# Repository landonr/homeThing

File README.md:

<h1 align = "center">homeThing Remote ⚙️</h1>
<h5 align = "center">(esphome remote)</h5>
<p align="center">

</p>

<br>
<div align="center">
	<h2>This project is no longer in active development</h2>
	<p>The homeThing S3 can still be <a href="https://www.pcbway.com/project/shareproject/homeThing_S3_2b3ac3ac.html">ordered fully assembled from PCBWay</a>. The code, case files, and PCB files stay here for anyone who wants to build their own.</p>
	<h3>The successor is <a href="https://github.com/landonr/homething-c6">homeThing C6</a></h3><p>a universal remote with a scroll wheel. It has no screen, better battery life, and also sponsored by PCBWay.</p>
</div>
<hr>

#### homeThing is a collection of software and hardware for creating universal remotes that control smart home devices.
There are 3 components that belong to homeThing: the case and circuit board, the menu system code, and the code to control smart home devices
- <a href="#hardware-">Hardware specific for smart home remotes that's open source, customizable, and 3D printable.</a>
- <a href="#homething-menu-">Menu system for ESP32 devices focused on controlling smart home devices similar to an iPod's menu.</a>
- [ESPHome Components for controlling Home Assistant devices.](https://github.com/landonr/esphome-components)

### Learn More
 - [Get Started](GettingStarted.md) - Learn how to build your own remote
 - [Discord](https://discord.gg/BX6ZtGKHTy) - support / chat with the community and the team
 - [Instagram](https://www.instagram.com/homething.io/) - Follow along on Instagram
 - [Website](https://homething.io) - Check out our website for more information

<div align="center">
	<h3>
	<a href="https://youtu.be/5bx5w-n5c0Y">
		
		<br>Demo Video - Watch on YouTube 🎬
	</a>
	</h3>
</div>

# Hardware 💪
We designed the two remotes below to be ideal for controlling smart home devices without a touch screen. They are both battery-powered but can also be plugged into USB and left in one place. The first remote was based on a Lilygo TDisplay. We moved on to the homeThing S3 because the original device had slow performance, lacked buttons, and had challenges with assembly. Neither is in active development anymore; work has moved to [homeThing C6](https://github.com/landonr/homething-c6).
<table>
  <tr>
    <th>
	    <h3>TDisplay homeThing</h3>
    </th>
    <th>
	    <h3>TDisplay S3 homeThing</h3>
	    <a href="https://github.com/landonr/homeThing/tree/main/Case%20Design/tdisplay-s3">More Info</a><br>
    </th>
  </tr>
  <tr>
    <td></td>
    <td></td>

  </tr>
  <tr>
	  <td>Not available for purchase</td>
	  <td>No longer developed, still available fully assembled from PCBWay</td>
  </tr>
  <tr>
    <td><a href="https://www.pcbway.com/project/shareproject/homeThing_V1_3_e3572f8f.html">Order Case from PCBWay</a></td>
    <td>
      <a href="https://www.pcbway.com/project/shareproject/homeThing_S3_2b3ac3ac.html">Order parts or fully assembled from PCBWay</a>
    </td>
  </tr>
  <tr>
    <td></td>
    <td>Sold: 27 assembled, 32 PCBs, 10 cases</td>
  </tr>
  <tr>
    <td><a href="https://github.com/landonr/homeThing/tree/main/Case%20Design">Case 3D Files</a></td>
    <td><a href="https://github.com/landonr/homeThing/tree/main/Case%20Design">Case 3D Files</a></td>
  </tr>
  <tr>
    <td><a href="tdisplay-ipod.yaml">ESPHome Config</a></td>
    <td><a href="tdisplay-s3.yaml">ESPHome Config</a></td>
  </tr>
  <tr>
  	<td>
	<h4>Features</h4>
	<ul>
		<li>Based on Lilygo TTGo TDisplay, an ESP32 with integrated screen
		<li>Low cost remote with minimal parts</li>
		<li>Scroll wheel and 2 configurable buttons</li>
		<li>USB-C Charging</li>
		<li>3D Printable case with 3 parts</li>
	</ul>
	</td>
  	<td>
	<h4>Features</h4>
	<ul>
		<li>Based on Lilygo TDisplay S3, an ESP32 S3 with integrated screen</li>
		<li>Faster processor and larger display</li>
		<li>Custom PCB for easier setup</li>
		<li>IR Blaster for controlling infrared devices</li>
		<li>Internal microphone for Voice Assistant</li>
		<li>Scroll wheel and 5 configurable buttons</li>
		<li>USB-C Charging</li>
		<li>3D Printable case with 2 parts</li>
	</ul>
	</td>
  </tr>
</table>

We made a couple of custom devices for running homeThing, but it can also run on almost any ESP32 such as,
- M5Stack Fire
- M5Stick C
- Lilygo T4
- Lilygo T-Display TTGO
- Lilygo T-Display S3
- Lilygo T-Display S3 AMOLED
# homeThing Menu 📝
### ESPHome menu system that requires minimal config. Features apps which have custom UIs
|t-display demo|m5stack fire demo|lilygo T4 demo|
|--|--|--|
|||

- Scroll through list and press center to select
- With a scrollwheel the top button goes back
- On M5Stack going up past the top of the list will go back
- A scroll bar appears if list extends past the screen. 
- Screen returns to now playing after display sleeps
    - Display sleeps after 10s of idle. Device sleeps after 2h of idle 💤
- Font size and UI size is adjustable in yaml 🔨
- Simple yaml configuration. all of the complicated code is included in other files 🛠
- Header is always shown at the top with info about the current state

## Apps
### Now playing screen ⏯

<ul>
<li>Control media players using the scroll wheel buttons</li>
<li>Scroll for volume using the scroll wheel</li>
</ul>

|Music|TV|
|--|--|
|<ul><li>Control smart speakers like Sonos, Spotify, or Google Home</li><li>Change source from Spotify playlists, Sonos Favorites, and custom lists</li><li>Manage speaker groups</li></ul>|<ul><li>Menu navigation such as up, down, left, right, select (with scroll wheel)</li><li>Power, back, home, pause in second menu</li><li>Change source from tv source list</li><li>Optional soundbar support</li></ul>|

### IR Remote
<ul>
<li>Custom UI and buttons to control infrared cat toys</li>
</ul>

### Games
<ul>
<li>Snake</li>
<li>Breakout</li>
</ul>

# Mentions
- Home Assistant Voice Contest - Best Starting Guide https://www.home-assistant.io/blog/2024/03/16/voice-assistant-community-contest-winners-annoucement/
- Hackaday https://hackaday.com/2022/09/08/scroll-through-esphome-with-ipod-style-click-wheel/
- Hackster https://www.hackster.io/news/ipod-style-esphome-remote-3ca38edab2b4
- Reddit post https://www.reddit.com/r/homeassistant/comments/x59dcp/i_built_an_ipod_style_esphome_remote_for_home/
- Self Hosted - Episode 80 - Solving Whole Home Audio (around 30:00) https://selfhosted.show/80 

# Includes
- <a href="https://esphome.io/">ESPHome</a>
- <a href="https://github.com/be5invis/Iosevka">Iosevka Font</a>
- [@ssieb](https://github.com/ssieb)'s <a href="https://github.com/ssieb/custom_components/tree/master/components/ip5306">IP5306 esphome component</a>
- <a href="https://github.com/landonr/esphome-components">homeThing ESPHome Components</a>

# Sponsorship

## [PCBWay](https://pcbway.com/g/Xymq6O "PCBWay") sponsored 3D Printing and PCB assembly costs on this project during the prototyping phase, and also sponsors [homeThing C6](https://github.com/landonr/homething-c6)!
If you are interested in their awesome fabrication services please check them out. They offer 3D prototyping, PCB design and assembly, as well as CNC metal fabrication. Costs are reasonable and the quality is as good as it gets. Thank you PCBWay for sponsoring us and other fun projects!<br><br>

## [cargo](https://cargo.site/ "cargo.site") sponsors our website!

They make it super easy to keep things pretty and up to date! It’s honestly so much easier than managing our own site, highly recommended!

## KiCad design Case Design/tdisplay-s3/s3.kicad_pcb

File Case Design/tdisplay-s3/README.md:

<h2>TDisplay S3 homeThing</h2>

This remote is no longer in active development. It can still be <a href="https://www.pcbway.com/project/shareproject/homeThing_S3_2b3ac3ac.html">ordered fully assembled from PCBWay</a>, and the files stay here for DIY builds. The successor is <a href="https://github.com/landonr/homething-c6">homeThing C6</a>, a universal remote with a scroll wheel, no screen, and better battery life.

<table>
    <tr>
        <th>TDisplay S3<br>homeThing Case</th>
        <th>homeThing S3<br>Circuit Front</th>
        <th>homeThing S3<br>Circuit Back</th>
    </tr>
    <tr>
        <td>
            
        </td>
        <td>
            
        </td>
        <td>
            
        </td>
    </tr>
</table>

<h2>Order</h2>
<a href="https://www.pcbway.com/project/shareproject/homeThing_S3_2b3ac3ac.html">Order Case and PCB from PCBWay</a>

Sold: 27 assembled, 32 PCBs, 10 cases

<h2>Case 3D Files</h2>
There's a separate front file for FDM printers. It has no extruded buttons, so it prints flat without supports.
<table>
    <tr>
        <th>Front (SLS)</th>
        <th>Front (FDM)</th>
        <th>Back</th>
    </tr>
    <tr>
        <td><a href="s3%20case%20front%20sls.stl">s3 case front sls.stl</a></td>
        <td><a href="s3%20case%20front%20fdm.stl">s3 case front fdm.stl</a></td>
        <td><a href="s3%20case%20back.stl">s3 case back.stl</a></td>
    </tr>
</table>

<h2>Circuit</h2>
<a href="gerber/">Gerber Files</a>

<h2>ESPHome Config</h2>
<a href="../../tdisplay-s3.yaml">tdisplay-s3.yaml</a>

<h2>Parts</h2>
<table>
    <tr>
        <th>Name</th>
        <th>Qty</th>
        <th>Description</th>
    </tr>
    <tr>
        <td><a href="https://www.pcbway.com/project/shareproject/homeThing_S3_2b3ac3ac.html">Custom PCB</a></td>
        <td>1</td>
        <td>Custom homeThing S3 PCB. Gerbers are in <a href="gerber/">gerber/</a>.</td>
    </tr>
    <tr>
        <td><a href="https://www.lilygo.cc/en-ca/products/t-display-s3?variant=42351558590645">TDisplay S3 (Soldered Pin)</a></td>
        <td>1</td>
        <td>ESP32-S3 board with screen. Plugs into the PCB.</td>
    </tr>
    <tr>
        <td><a href="https://www.adafruit.com/product/5001">Adafruit ANO Directional Navigation and Scroll Wheel Rotary Encoder</a></td>
        <td>1</td>
        <td>Directional buttons and scroll wheel</td>
    </tr>
    <tr>
        <td><a href="https://www.adafruit.com/product/5221">Adafruit ANO Rotary Navigation Encoder Breakout PCB</a></td>
        <td>1</td>
        <td>Breakout for the ANO encoder. Plugs into the PCB.</td>
    </tr>
    <tr>
        <td><a href="https://www.aliexpress.us/item/32962426410.html">INMP441</a></td>
        <td>1</td>
        <td>I2S microphone</td>
    </tr>
    <tr>
        <td><a href="https://leeselectronic.com/en/product/71446-ic-i-o-expander-for-i2c-8bit-pcf8574p.html">PCF8574N</a></td>
        <td>1</td>
        <td>I2C GPIO expander for the ANO and case buttons</td>
    </tr>
    <tr>
        <td><a href="https://www.adafruit.com/product/387">5mm 940nm IR LED</a></td>
        <td>1</td>
        <td>IR transmitter on GPIO13</td>
    </tr>
    <tr>
        <td><a href="https://leeselectronic.com/qc/product/7174-7174TRANSISTOR2N2222MPS2222ANPN5.html">2N2222 NPN transistor</a></td>
        <td>1</td>
        <td>IR LED driver</td>
    </tr>
    <tr>
        <td><a href="https://leeselectronic.com/en/product/91581-91581RESISTORS14W470OHM110PCS.html">470ohm resistor</a></td>
        <td>1</td>
        <td>IR LED current limit</td>
    </tr>
    <tr>
        <td><a href="https://leeselectronic.com/en/product/844-polyester-cap-50v-01uf-4pcs.html">0.1uF capacitor</a></td>
        <td>1</td>
        <td>Decoupling for the PCF8574</td>
    </tr>
    <tr>
        <td><a href="https://leeselectronic.com/en/product/31231-tack-switch-6x6x10mm.html">6x6mm tactile switch (10mm tall)</a></td>
        <td>3</td>
        <td>Through-hole tact switches for the case buttons</td>
    </tr>
    <tr>
        <td><a href="https://www.aliexpress.com/item/32835179410.html">3.7V 7x20x50mm 700mAh Lipo</a></td>
        <td>1</td>
        <td>Battery</td>
    </tr>
    <tr>
        <td><a href="https://leeselectronic.com/en/product/6049-6049BOLTM25100PCS.html">M2.5x8mm screws</a></td>
        <td>6</td>
        <td>Case screws</td>
    </tr>
    <tr>
        <td>Female pin socket 1x12, 2.54mm</td>
        <td>2</td>
        <td>T-Display S3 plugs into these</td>
    </tr>
    <tr>
        <td>Female pin socket 1x09, 2.54mm</td>
        <td>1</td>
        <td>ANO breakout plugs into this</td>
    </tr>
    <tr>
        <td>Female pin socket 1x03, 2.54mm</td>
        <td>2</td>
        <td>INMP441 plugs into these</td>
    </tr>
    <tr>
        <td>Male pin header 1x04, 2.54mm (optional)</td>
        <td>1</td>
        <td>Optional expansion header: 5V, GPIO12, GPIO16, GND</td>
    </tr>
</table>

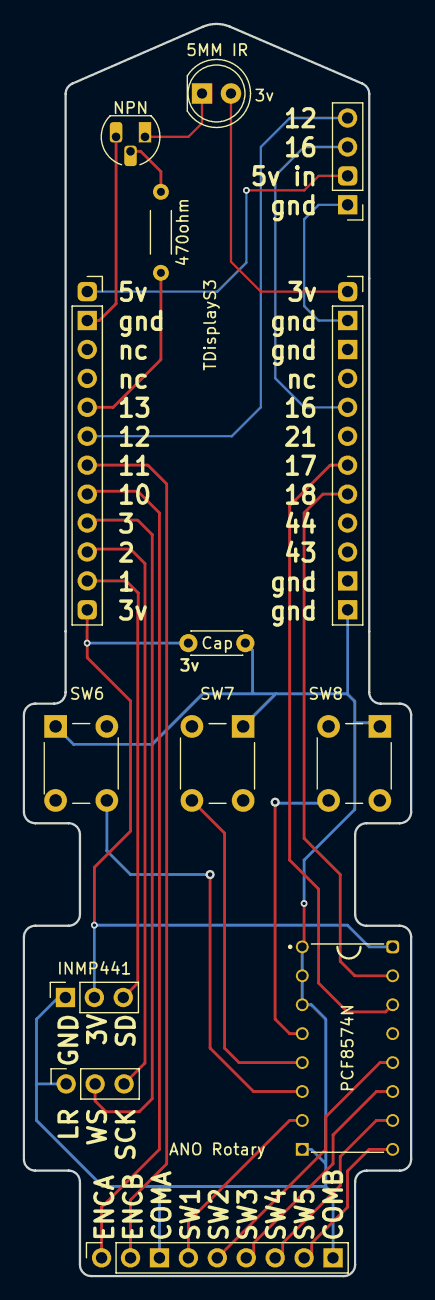
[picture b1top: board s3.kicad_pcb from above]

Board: 2 copper layers, 34.0 x 109.9 mm, 12 parts (0 on the bottom side), 17 nets.

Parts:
5MM IR: LED_D5.0mm_Clear
470ohm: R_Axial_DIN0204_L3.6mm_D1.6mm_P5.08mm_Horizontal
ANO Rotary: PinSocket_1x09_P2.54mm_Vertical
Cap: C_Disc_D4.3mm_W1.9mm_P5.00mm
INMP441, INMP441 2: PinSocket_1x03_P2.54mm_Vertical
NPN: TO-92L_HandSolder
PCF8574N: DIP794W45P254L1969H508Q16
SW6, SW7, SW8: SW_PUSH_6mm_H9.5mm
TDisplayS3: PinSocket_1x12_P2.54mm_Vertical

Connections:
3v: Cap.1, INMP441.2, PCF8574N.16, TDisplayS3.12
enca: ANO Rotary.ENCA, TDisplayS3.8
encb: ANO Rotary.ENCB, TDisplayS3.7
ground: ANO Rotary.COMA, ANO Rotary.COMB, Cap.2, INMP441.1, INMP441 2.1, PCF8574N.A0, PCF8574N.A1, PCF8574N.A2, PCF8574N.GND, SW6.1, SW7.2, SW8.2
ground2: NPN.3, TDisplayS3.gnd
irled: 5MM IR.1, 470ohm.1, 470ohm.2, NPN.1, NPN.2, TDisplayS3.5
sck: INMP441 2.3, TDisplayS3.10
sd: INMP441.3, TDisplayS3.11
sw1: ANO Rotary.SW1, PCF8574N.P3
sw2: ANO Rotary.SW2, PCF8574N.P7
sw3: ANO Rotary.SW3, PCF8574N.P6
sw4: ANO Rotary.SW4, PCF8574N.P5
sw5: ANO Rotary.SW5, PCF8574N.P4
sw6: PCF8574N.P2, SW6.2
sw7: PCF8574N.P1, SW7.1
sw8: PCF8574N.P0, SW8.1
ws: INMP441 2.2, TDisplayS3.9

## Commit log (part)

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2023-09-25 use branch
2023-09-25 dont use package for fire
2023-09-25 add now playing app
2023-09-25 fix casing on includes
2023-09-25 format
2023-09-25 Lando/refactor now playing (#77)
    * start refactoring now playing into its own file so we can replace it
    * menu loads now playing items
    * select screens works again
    * select sources is working
    * you can see now playing again
    * fix option menu select
2023-09-26 tune up the apps real nice
2023-10-04 add social share psd
2023-10-04 fix bugs with snake game
2023-10-05 fix grouping on now playing. move to files (#80)
2023-10-05 allow only apps
2023-10-07 fix switch on home screen not showing icon
2023-10-10 make a switch for dark mode (#81)
    fix light mode issues
2023-10-10 change log to debug
2023-10-10 fix vtable issue
2023-10-10 clear option menu if you press a button
2023-10-10 breakout game (#82)
    * update breakout
    * fix vtable issue
    * format
    * let rotary update screen optionally
2023-10-20 fix wrapped text memory issue reload menu if app needs it
2023-10-20 reset games when you go to top menu
2023-10-20 add rotary comments
2023-10-22 fix option menu not working!
2023-10-22 fix backlight not turning off on tdisplay
2023-10-24 hold switch c button to reboot or select
2023-10-24 fix now playing not going to root
2023-10-24 use esp32 rmt instead of fastled because of warnings
2023-10-24 add fire binary sensor rotary
2023-10-25 fix boot showing if not set
2023-10-29 organize case files and add kicad file
2023-10-29 add s3 case stl and f3z files
2023-10-30 change led to 5mm and add transistor to it
2023-10-30 fix ground not connecting to bottom pin
2023-11-08 update cap to be between 3v and gnd for i2c
2023-11-08 make super basic config
2023-11-08 add basic to ci
2023-11-08 update track thickness
2023-11-09 update boot to not require media players
2023-11-09 fix image dependency
2023-11-09 use main branch
2023-11-09 add local and roboto shared yamls
2023-11-09 remove external components from s3
2023-11-09 remove space from logo
2023-11-09 update font name
2023-11-09 remove font component
2023-11-09 use branch for component
2023-11-09 use roboto and local images (#90)
    * use roboto and local images
    * remove external components from s3
    * update a few more devices
    * update font name
    * remove font component
    * fix media player stuff in boot leftover
2023-11-10 add automation triggers for easier configs
2023-11-11 use automation everywhere
2023-11-11 fix rotary scroll command
2023-11-11 typo
2023-11-11 fix branch name
2023-11-11 reroute transistor
2023-11-14 add toggle on home screen for media players
2023-11-14 add idle app option to settings
2023-11-14 add automation triggers for easier configs (#91)
    * add automation triggers for easier configs
    * format
    * add select and change select hold to option
    * format
    * use automation everywhere
    * use branch
2023-11-14 fix errors building with espressif
2023-11-15 update branch and add debug
2023-11-15 change logs to debug
2023-11-15 fix all but light warnings
2023-11-15 cpplint
2023-11-15 move source to its own file
2023-11-15 fix sensor not showing value
2023-11-17 more readme updates!
2023-11-17 add s3 dxf and kicad pcb (#87)
    * add s3 dxf and kicad pcb
    * organize case files and add kicad file
    * add s3 case stl and f3z files
    * change led to 5mm and add transistor to it
    * fix ground not connecting to bottom pin
    * add capacitor to i2c
2023-11-17 add weather yaml
2023-11-17 add launch image to weather
2023-11-17 add weather app (#93)
    * add weather app
    * add weather yaml
    * add launch image to weather
    * add weather to tdisplay
2023-11-24 update s3 config
2023-11-24 update s3 again
2023-11-24 remove image pr
2023-11-26 show light effects in light detail
2023-12-05 fix scrolling with double line rows
2023-12-06 update pcf config for circuit
2023-12-08 add notifications that show over the ui
2023-12-08 Notifications (#95)
    * add notifications that show over the ui
    * fix log
2023-12-08 remove boot logo size and get the height from the image instead
2023-12-30 move launch image to boot config
2023-12-30 fix weather app
2023-12-30 fix more devices
2023-12-30 add stick backlight pin
2023-12-30 revert branch
2023-12-30 move launch image to boot config (#96)
    * move launch image to boot config
    * update configs to match new schema
    * fix weather app
    * format
    * fix more devices
    * clean up stick sleep
2024-01-09 5000 mAh battery case
    Case design to fit the T-display with a 5000 mAh battery.
    The original buttons are used.
2024-01-10 Renamed files to be a bit more descriptive
2024-01-12 5000 mAh battery case (#97)
    * 5000 mAh battery case
    Case design to fit the T-display with a 5000 mAh battery.
    The original buttons are used.
    * Renamed files to be a bit more descriptive
    * added readme file + main components picture
    * Update README.md
2024-01-14 add now playing image
2024-01-15 replace external component ref
2024-01-15 update s3 ref
2024-01-16 fix margin on bottom menu
2024-01-16 update s3 example to use pcb and media player image
2024-01-16 add ref for components
2024-01-16 add now playing image (#98)
    * add now playing image
    * replace branch reference with current branch
    * replace external component ref
    * update s3 ref
    * fix now playing bottom bar position
    * fix margin on bottom menu
2024-01-22 fix now playing bottom menu not showing when option is set
2024-01-23 update s3 now playing to package
2024-01-23 fix now playing bottom menu not showing when option is set (#99)
    * fix now playing bottom menu not showing when option is set
    * fix megadesk config
    * update s3 now playing to package
    * add logger.yaml
2024-01-23 update readme and add nowplayingimage package
2024-01-23 fix menu boot now palying image
2024-01-24 add files for s3 case
2024-02-05 add s3 readme
2024-02-06 Rename s3circuit.png to s3Circuit.png
2024-02-17 add python pillow to ci
2024-02-17 update action
2024-02-17 add requirements back
2024-02-17 remove e
2024-02-27 add python pillow to ci (#102)
    * add python pillow to ci
    * update pillow version
    * update action
    * add requirements back
    * add more requirements and pip e
    * remove e
2024-02-27 add max brightness
2024-03-21 update case files
2024-03-21 add max brightness (#103)
    * add max brightness
    * format
2024-03-24 remove allow other uses from ipod config
2024-03-27 Addis Some i2c That should work.
2024-03-27 Changed all i2c files to "seesaw" for clarity
2024-03-27 added to comments to show what is pfc and what is seesaw. Also removed extra tdisplay yaml
2024-03-28 Change package location back to orriginal
2024-03-28 update package ref for current branch
2024-03-28 undo seesaw change
2024-03-28 update ci action
2024-03-28 add note about images needing pillow
2024-03-28 undo other seesaw change
2024-04-05 update s3 case increase clearances between front and back case add support behind pcb by buttons
2024-04-05 add voice assistant yaml
2024-04-05 Fix s3 config (#110)
    * update s3 config
    * add voice assistant yaml
2024-04-06 no message
2024-04-06 generate esphome devices automatically (#111)
    * generate esphome devices automatically
    * no message
    * no message
    * no message
    * no message
    * no message
2024-04-06 dont create face secrets
2024-04-06 debug
2024-04-06 update local build to replace with branch
2024-04-07 update ap text
2024-04-07 update every config to use device base wifi
2024-04-07 remove font pr include because its in main
2024-04-07 add progress for access point state
2024-04-08 add pcf address to substitutions
2024-04-22 update case files to match orders
2024-04-23 add white logo
2024-04-25 null check for active menu before setting it
2024-04-25 add device base light
2024-04-25 add comments
2024-04-25 Boot crash fix (#115)
    * fix menu selection when skipping boot, and crash on now playing without player
    * update launch image url
    * add device base light
    * update wifi settings for ipod
    * add comments
    * remove #update_to_head_ref
2024-04-25 add boot to tdisplay ipod
2024-04-26 add secrets back (#117)
2024-04-27 add automations for notifications add types and automation python files
2024-04-28 update s3 and voice assistant yaml
2024-04-28 add automation readme
2024-04-30 remove desk screen from s3 config
2024-05-11 add factory reset switch
2024-05-11 add reset switch to settings screens
2024-05-11 fix voice assistant notifications
2024-05-23 add camera app
2024-05-25 fix marquee scrolling to weird positions when user is scrolling
2024-05-26 pcb updates add 3v + symbol to LED add pcf8574n up symbol make resistor gap larger
2024-05-28 update getting started, add homething config readme
2024-05-28 try relative link
2024-05-28 update getting started, add homething config readme (#123)
    * update getting started, add homething config readme
    * add component readme and update links
    * try relative link
    * no message
    * no message
2024-06-02 add new fan menu item
2024-06-02 add other weather images
2024-06-02 add 3v to capacitor, update image
2024-06-02 show fan as switch
2024-06-02 fix toggle on fan
2024-06-20 add partly cloudy and lightning
2024-06-20 add ota platform
2024-06-20 add ota platform (#127)
2024-06-20 add i2c package
2024-06-20 upgrade build action version
2024-06-20 June24 (#128)
    * add ota platform
    * remove logger from device base
    * add i2c package
    * upgrade build action version
    * upgrade esphome builder version
2024-06-21 update s3 weather config
2024-06-21 add all the weather states (#125)
    * add all the weather states
    * add other weather images
    * format
    * add partly cloudy and lightning
    * remove duplicate lightning case
    * update s3 weather config
2024-06-22 update ipod and weather yaml
2024-06-22 Fan menu item and component (#124)
    * add new fan menu item
    * format
    * add fan images
    * show fan as switch
    * fix toggle on fan
    * format
2024-07-01 Show sensor value before name. add menu item renaming (#129)
    * update sensor menu item so value is first. add name as optional param
    * add option to rename menu items
    * update s3 config
    * fix fan menu item
    * fix fan menu item
    * format
2024-07-01 fix app animation
2024-07-01 update pcb image
2024-07-01 add select menu item
2024-07-01 add select menu item (#131)
2024-07-05 add active player sensor
2024-07-05 add unit of measurement
2024-07-05 add missing break
2024-07-05 Sensor value on right of screen (#134)
    * move sensor value to right of menu item
    * add unit of measurement
    * format
    * add missing break
    * build debug with current branch
2024-07-05 remote https from readme and update docs
2024-07-06 add now playing readme
2024-07-06 relative urls
2024-07-06 add more links to home and now playing
2024-07-06 fix link again
2024-07-06 add website link
2024-07-17 remove media calls from basic configs
2024-07-17 add i2c
2024-07-25 fix compile error for online_image (#137)
2024-07-31 add s3 without media player config
2024-08-13 add format to online image
2024-09-24 fix i2c address
2024-11-27 remove online image from s3 config
2024-11-27 fix missing glyphs
2024-11-27 add invert colors to m5stack fire
2024-11-27 invert colors in debug
2025-02-28 fix images for s3 config (#145)
2025-02-28 update config to new esphome
2025-03-10 update esphome github action to latest
2025-03-10 update github action parameter
2025-08-27 update esphome runner
2025-08-27 add home assistant states to device base
2025-08-27 update esphome runner (#147)
    * update esphome runner
    * fix rmt channel
    * add home assistant states to device base
    ---------
2025-08-27 add logger to failing devices
2025-08-27 remove stickcplus
2025-08-28 update tdisplay s3 to use espidf
2025-09-24 add base s3 amoled config
